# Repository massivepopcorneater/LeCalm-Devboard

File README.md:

# LeCalm-Devboard
LeCalm Devboard is a open-source devboard built around the Raspberry Pi RP2040 microcontroller. It features a USB-C connector for programming and power, an onboard 3.3V regulator, a 16MB flash chip, and a 12MHz crystal oscillator for precise timing. The board includes a BOOTSEL button for firmware flashing.
This project was designed in KiCad as a personal learning project, exploring PCB layout, component selection, and design for manufacture with JLCPCB.

## Schematic

The schematic of the LeCalm Devboard centers around the RP2040 microcontroller. The power section takes 5V from the USB-C connector and passes it through the MCP1700 LDO regulator to produce a clean 3.3V rail, with 1uF and 10uF bulk capacitors smoothing out any voltage fluctuations. Each power pin on the RP2040 is decoupled with a dedicated 0.1uF capacitor placed as close to the pin as possible to suppress high frequency noise. The 12MHz crystal oscillator is connected to the XIN and XOUT pins of the RP2040 with two 33pF load capacitors to ground, providing the precise clock reference needed for full speed operation and stable USB communication. The USB-C connector is wired with 5.1K resistors on the CC1 and CC2 configuration pins for proper power negotiation, and 27Ω series resistors on the D+ and D- differential pair to reduce signal reflections. The W25Q128JVS flash chip is connected to the RP2040 via SPI with all power pins properly decoupled, and the BOOTSEL button is wired to the flash chip select line through a current limiting resistor to ground, allowing the RP2040 to enter USB Mass Storage mode on boot when pressed.

## PCB Design

The PCB layout of the LeCalm Devboard was designed in KiCad with a focus on signal integrity and clean power distribution.  Decoupling capacitors are placed as close as physically possible to the power pins of the RP2040 and the W25Q128JVS flash chip to minimize trace inductance and ensure effective high frequency filtering. The 12MHz crystal oscillator is positioned close to the XIN and XOUT pins of the RP2040 to keep the clock traces short and reduce the risk of noise pickup. The USB-C connector is placed at the edge of the board for easy access, with the 27Ω series resistors on the D+ and D- differential pair routed as a matched length pair to maintain signal integrity across the USB data lines. A ground copper pour covers both the front and back copper layers, providing a low impedance return path for all signals and helping to dissipate heat across the board. Thermal relief spokes are used where pads connect to the ground pour to ensure reliable soldering during assembly. The BOOTSEL button is positioned on the top of the board for easy access during firmware flashing. All SMD components use 0402 and 0603 imperial footprints, keeping the overall board size compact while remaining manufacturable through JLCPCBs standard PCB assembly service.

## Bill of Materials
| Designation | Designation | JLCPCB Part # | Value | Footprint |
| ------------|-------------|---------------|-------|-----------|
| Capacitor | C1, C10 | C52923 | 1uF | C_0402_1005Metric |
| Capacitor | C2, C3, C4, C5, C6, C7, C8, C9, C11, C12, C17 | C1525 | 0.1uF | C_0402_1005Metric |
| Capacitor | C13, C14 | C19702 | 10uF | C_0603_1608Metric |
| Capacitor | C15, C16 | C1562 | 33pF | C_0402_1005Metric |
| USB_C Power | J1 | C165948 | USB_C_Receptacle_USB2.0_14P | USB_C_Receptacle_HRO_TYPE-C-31-M-12 |
| Resistor | R1, R2 | C25905 | 5.1K | R_0402_1005Metric |
| Resistor | R3, R4 | C25100 | 27Ω | R_0402_1005Metric |
| Resistor | R5, R6 | C11702 | 1K | R_0402_1005Metric |
| Resistor | R7 | C25744 | 10K | R_0402_1005Metric |
| Bootsel Button | SW1 | C720477 | SW_Push | SW_Push_SPST_NO_Alps_SKRK |
| Microcontroller | U1 | C2040| RP2040 | QFN-56-1EP_7x7mm_P0.4mm_EP3.2x3.2mm |
| LDO | U2 | C39051 | MCP1700x-120xxTT | SOT-23 |
| Flash Memory | U3 | C2843335 | W25Q128JVS | Winbond_USON-8-1EP_3x2mm_P0.5mm_EP0.2x1.6mm |
| Crystal Oscillator | Y1 | C9002 | 12MHz | Crystal_SMD_Abracon_ABM8-2Pin_3.2x1.5mm |

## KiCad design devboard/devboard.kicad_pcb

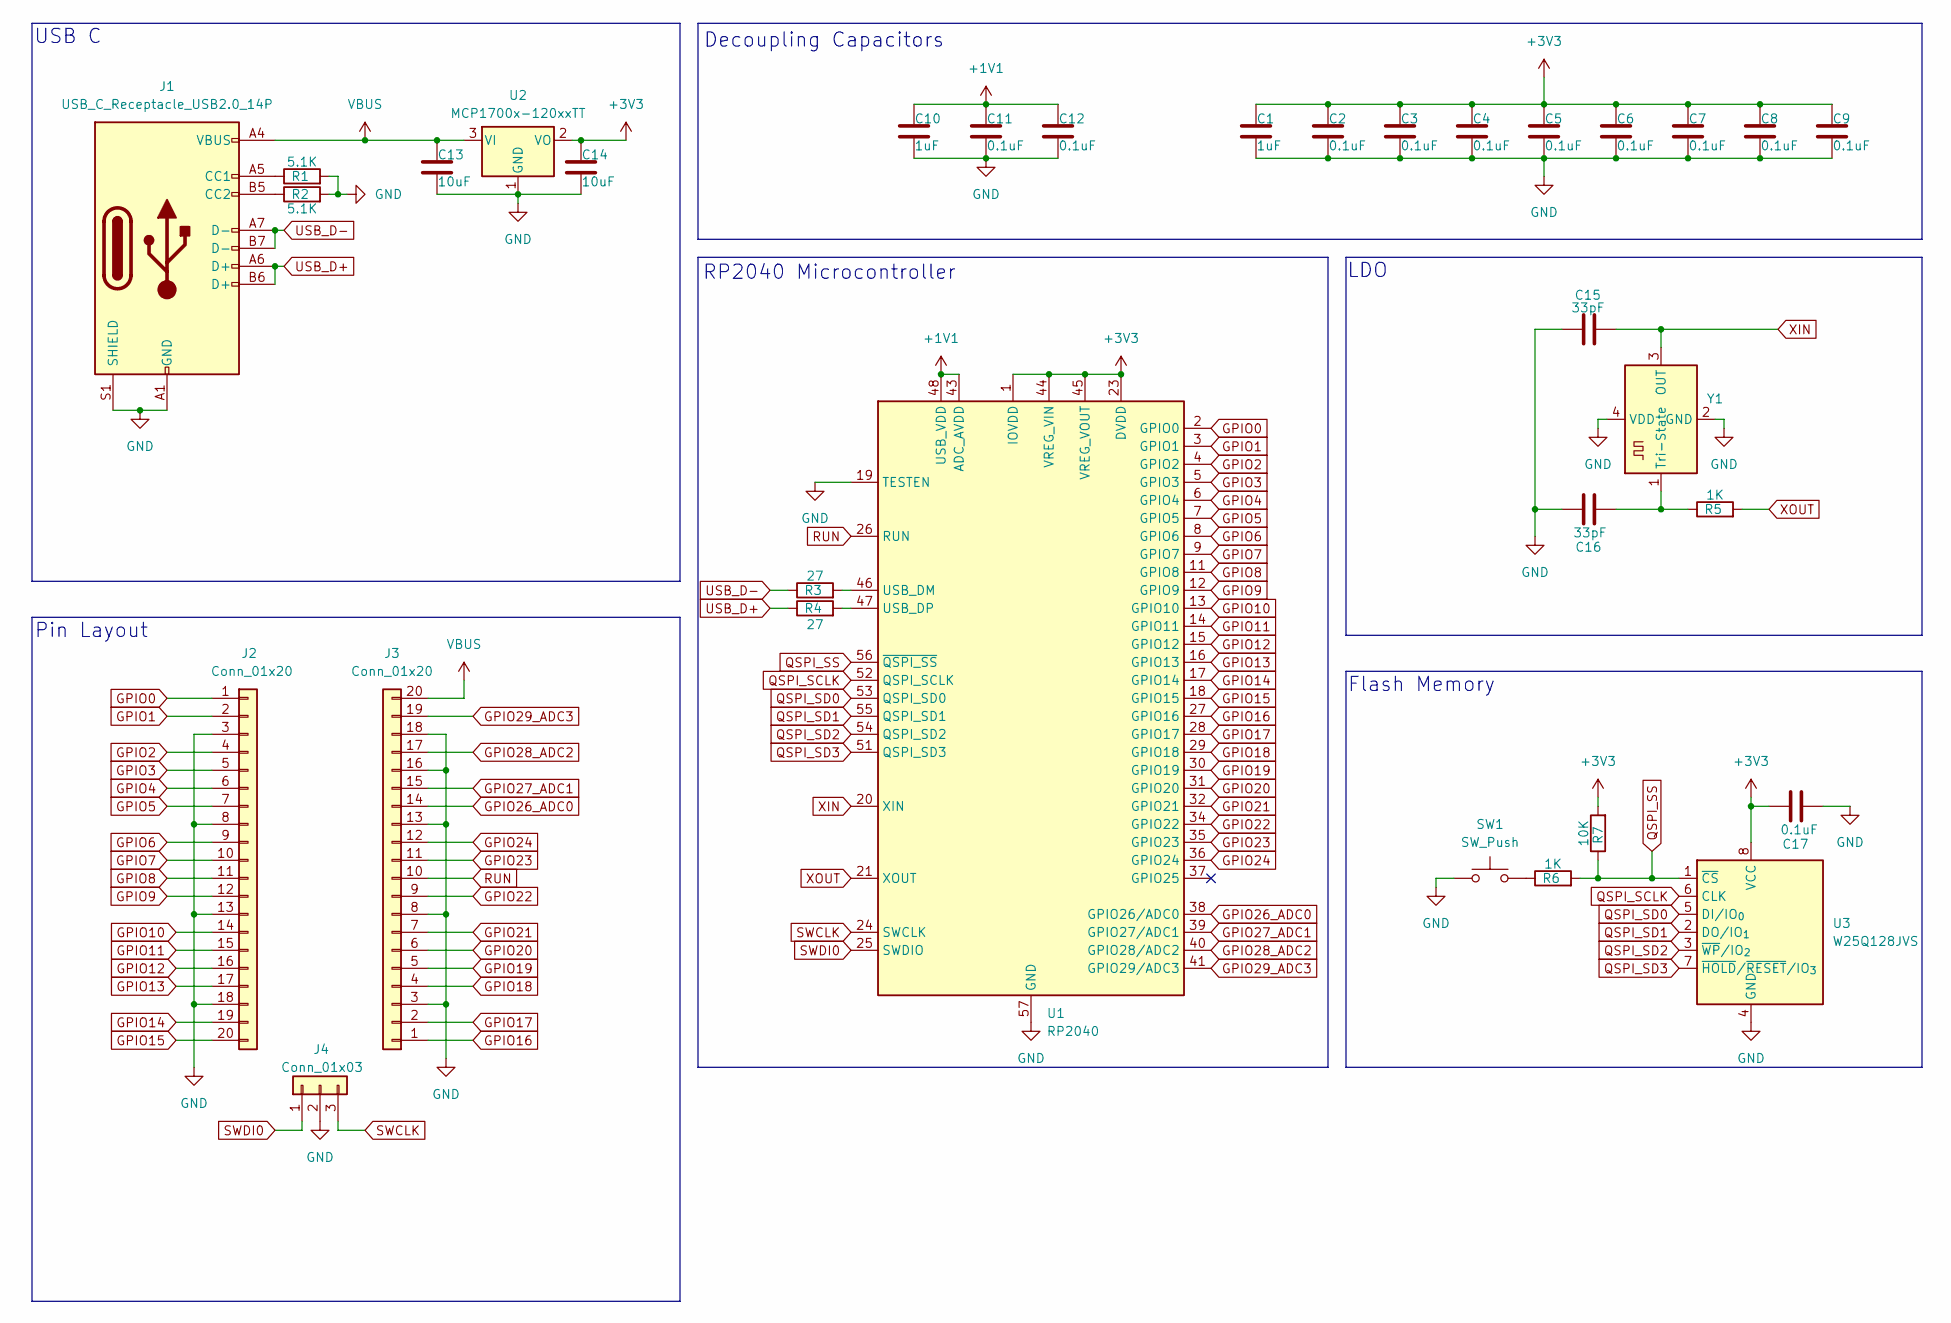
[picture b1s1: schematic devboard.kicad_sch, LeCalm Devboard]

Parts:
C1, C10: 1uF; C_0402_1005Metric
C2, C3, C4, C5, C6, C7, C8, C9, C11, C12, C17: 0.1uF; C_0402_1005Metric
C13, C14: 10uF; C_0603_1608Metric
C15, C16: 33pF; C_0402_1005Metric
J1: USB_C_Receptacle_USB2.0_14P; USB_C_Receptacle_HRO_TYPE-C-31-M-12
J2, J3: Conn_01x20; PinHeader_1x20_P2.54mm_Vertical
J4: Conn_01x03; PinHeader_1x03_P2.54mm_Vertical
R1, R2: 5.1K; R_0402_1005Metric
R3, R4: 27; R_0402_1005Metric
R5, R6: 1K; R_0402_1005Metric
R7: 10K; R_0402_1005Metric
SW1: SW_Push; SW_Push_SPST_NO_Alps_SKRK
U1: RP2040; QFN-56-1EP_7x7mm_P0.4mm_EP3.2x3.2mm
U2: MCP1700x-120xxTT; SOT-23
U3: W25Q128JVS; Winbond_USON-8-1EP_3x2mm_P0.5mm_EP0.2x1.6mm
Y1: 12MHz; Crystal_SMD_3225-4Pin_3.2x2.5mm

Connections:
+1V1: C10.1, C11.1, C12.1, U1.43 (ADC_AVDD), U1.48 (USB_VDD)
+3V3: C1.1, C2.1, C3.1, C4.1, C5.1, C6.1, C7.1, C8.1, C9.1, C14.1, C17.2, R7.2, U1.1 (IOVDD), U1.10 (IOVDD), U1.22 (IOVDD), U1.23 (DVDD), U1.33 (IOVDD), U1.42 (IOVDD), U1.44 (VREG_VIN), U1.45 (VREG_VOUT), U1.49 (IOVDD), U1.50 (DVDD), U2.2 (VO), U3.8 (VCC)
GND: C1.2, C2.2, C3.2, C4.2, C5.2, C6.2, C7.2, C8.2, C9.2, C10.2, C11.2, C12.2, C13.2, C14.2, C15.1, C16.2, C17.1, J1.A1 (GND), J1.A12 (GND), J1.B1 (GND), J1.B12 (GND), J1.S1 (SHIELD), J2.3, J2.8, J2.13, J2.18, J3.3, J3.8, J3.13, J3.16, J3.18, J4.2, R1.2, R2.2, SW1.1, U1.19 (TESTEN), U1.57 (GND), U2.1 (GND), U3.4 (GND), Y1.2 (GND), Y1.4 (VDD)
GPIO0: J2.1, U1.2 (GPIO0)
GPIO1: J2.2, U1.3 (GPIO1)
GPIO2: J2.4, U1.4 (GPIO2)
GPIO3: J2.5, U1.5 (GPIO3)
GPIO4: J2.6, U1.6 (GPIO4)
GPIO5: J2.7, U1.7 (GPIO5)
GPIO6: J2.9, U1.8 (GPIO6)
GPIO7: J2.10, U1.9 (GPIO7)
GPIO8: J2.11, U1.11 (GPIO8)
GPIO9: J2.12, U1.12 (GPIO9)
GPIO10: J2.14, U1.13 (GPIO10)
GPIO11: J2.15, U1.14 (GPIO11)
GPIO12: J2.16, U1.15 (GPIO12)
GPIO13: J2.17, U1.16 (GPIO13)
GPIO14: J2.19, U1.17 (GPIO14)
GPIO15: J2.20, U1.18 (GPIO15)
GPIO16: J3.1, U1.27 (GPIO16)
GPIO17: J3.2, U1.28 (GPIO17)
GPIO18: J3.4, U1.29 (GPIO18)
GPIO19: J3.5, U1.30 (GPIO19)
GPIO20: J3.6, U1.31 (GPIO20)
GPIO21: J3.7, U1.32 (GPIO21)
GPIO22: J3.9, U1.34 (GPIO22)
GPIO23: J3.11, U1.35 (GPIO23)
GPIO24: J3.12, U1.36 (GPIO24)
GPIO26_ADC0: J3.14, U1.38 (GPIO26/ADC0)
GPIO27_ADC1: J3.15, U1.39 (GPIO27/ADC1)
GPIO28_ADC2: J3.17, U1.40 (GPIO28/ADC2)
GPIO29_ADC3: J3.19, U1.41 (GPIO29/ADC3)
unnamed: J1.A5 (CC1), R1.1
unnamed: J1.B5 (CC2), R2.1
unnamed: R6.1, SW1.2
unnamed: R3.2, U1.46 (USB_DM)
unnamed: R4.2, U1.47 (USB_DP)
unnamed: C16.1, R5.1, Y1.1 (Tri-State)
QSPI_SCLK: U1.52 (QSPI_SCLK), U3.6 (CLK)
QSPI_SD0: U1.53 (QSPI_SD0), U3.5 (DI/IO_{0})
QSPI_SD1: U1.55 (QSPI_SD1), U3.2 (DO/IO_{1})
QSPI_SD2: U1.54 (QSPI_SD2), U3.3 (~WP/IO_{2})
QSPI_SD3: U1.51 (QSPI_SD3), U3.7 (~HOLD/~RESET/IO_{3})
QSPI_SS: R6.2, R7.1, U1.56 (~QSPI_SS), U3.1 (~CS)
RUN: J3.10, U1.26 (RUN)
SWCLK: J4.3, U1.24 (SWCLK)
SWDI0: J4.1, U1.25 (SWDIO)
USB_D+: J1.A6 (D+), J1.B6 (D+), R4.1
USB_D-: J1.A7 (D-), J1.B7 (D-), R3.1
VBUS: C13.1, J1.A4 (VBUS), J1.A9 (VBUS), J1.B4 (VBUS), J1.B9 (VBUS), J3.20, U2.3 (VI)
XIN: C15.2, U1.20 (XIN), Y1.3 (OUT)
XOUT: R5.2, U1.21 (XOUT)

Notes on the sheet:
USB C
Flash Memory
Pin Layout
LDO
Decoupling Capacitors
RP2040 Microcontroller

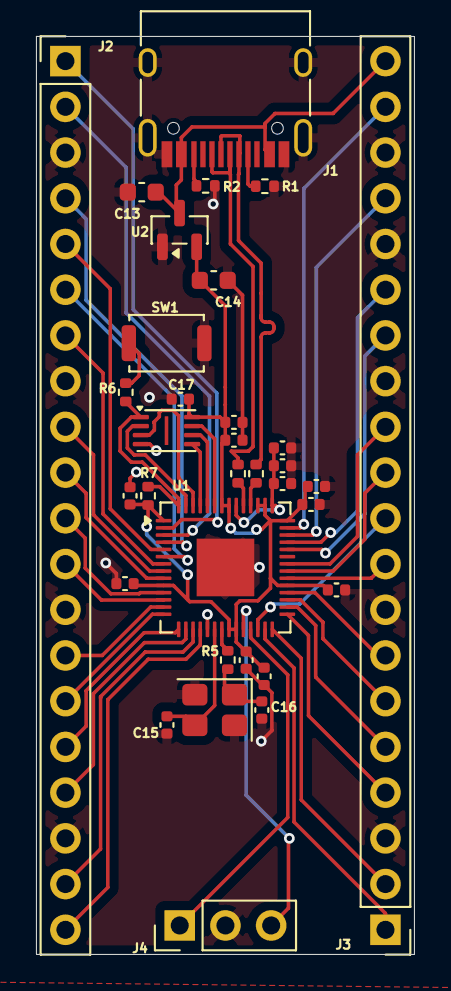
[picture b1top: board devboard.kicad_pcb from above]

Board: 2 copper layers, 21.0 x 51.0 mm, 33 parts (0 on the bottom side), 52 nets.

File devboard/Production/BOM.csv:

Id,Designator,Footprint,Quantity,Comment,Supplier and ref
1,"C14,C13",C_0603_1608Metric,2,10uF,
2,"C1,C10",C_0402_1005Metric,2,1uF,
3,"C2,C3,C4,C5,C6,C7,C8,C9,C11,C12,C17",C_0402_1005Metric,11,0.1uF,
4,"C15,C16",C_0402_1005Metric,2,33pF,
5,J1,USB_C_Receptacle_HRO_TYPE-C-31-M-12,1,USB_C_Receptacle_USB2.0_14P,
6,"J2,J3",PinHeader_1x20_P2.54mm_Vertical,2,Conn_01x20,
7,J4,PinHeader_1x03_P2.54mm_Vertical,1,Conn_01x03,
8,"R1,R2",R_0402_1005Metric,2,5.1K,
9,"R3,R4",R_0402_1005Metric,2,27,
10,"R5,R6",R_0402_1005Metric,2,1K,
11,R7,R_0402_1005Metric,1,10K,
12,SW1,SW_Push_SPST_NO_Alps_SKRK,1,SW_Push,
13,U1,QFN-56-1EP_7x7mm_P0.4mm_EP3.2x3.2mm,1,RP2040,
14,U2,SOT-23,1,MCP1700x-120xxTT,
15,U3,Winbond_USON-8-1EP_3x2mm_P0.5mm_EP0.2x1.6mm,1,W25Q128JVS,
16,Y1,Crystal_SMD_3225-4Pin_3.2x2.5mm,1,12MHz,

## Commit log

2026-02-10 file creation
2026-02-25 Finished basic schematic of Devboard 1.0
    The schematics of the devboard with basic functionalities was finished.
2026-03-01 PCB Starter
2026-03-01 Kalm
2026-03-01 PCB routing and changes
2026-03-01 Production file generation + final pcb update
2026-03-02 Added pictures folder
2026-03-04 final fr
